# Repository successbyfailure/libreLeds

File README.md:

# libreLeds
#### Free Software and Hardware designs for controling led ligths.
libreLeds is a combination of firmware, control app and pcbs that allows you to build led_enabled gadgets. 
#### All libre for you!.

### Getting started:

 -Flash firmware on the esp8266 via arduino ide.

 -Flash extra data via:
 https://github.com/esp8266/arduino-esp8266fs-plugin

 -Install app on your phone, set it to host a wifi AP named "ledMaster" with pass "clubmate", also make sure it will be 192.168.43.1 (default on android).

 -Fire the app and turn on the esp8266, it should autoconnect to the app.
 
 -Configure Wifi and led Settings
 
 -Enjoy!

### Hardware compatible:

 -WS2812 (aka Neopixel) Strip & matrix(single & chained) through NeoPixel & NeoMatrix Library.

 -APA102 (aka DotStar)  Strip & matrix(single & chained) through FastLed Library
 
 -WS2801

### LedGadget
....

### Features:

 -Control through QT app(linux/android/mac/win).

 -Artnet support (DMX over wifi).

 -Music analizer with MSGEQ7 (vuLevel, spectrum, peak, bpms)

 -Color Effects.

 -Effect Playlist.

 -Http Updater.

 -Http file uploader.

### Known things:
 -Stop the animations before changing the led config, shit can happen otherwise.
 -In AP mode there is a memory leak and in some minutes you loose remote control.

### Setup environment:
-Compile firmware:
You will need latest arduino with esp8266 support from:
https://github.com/esp8266/Arduino
Fastled Library from:
https://github.com/FastLED/FastLED/releases
Neopixel, matrix and gfx from adafruit.
https://learn.adafruit.com/adafruit-arduino-ide-setup/arduino-1-dot-6-x-ide

the libraries included in the dependencies folder.

-Compile app
latest QT for the desktop app, also android sdk for compiling android app.

### Wifi Modes:
...Explain here...

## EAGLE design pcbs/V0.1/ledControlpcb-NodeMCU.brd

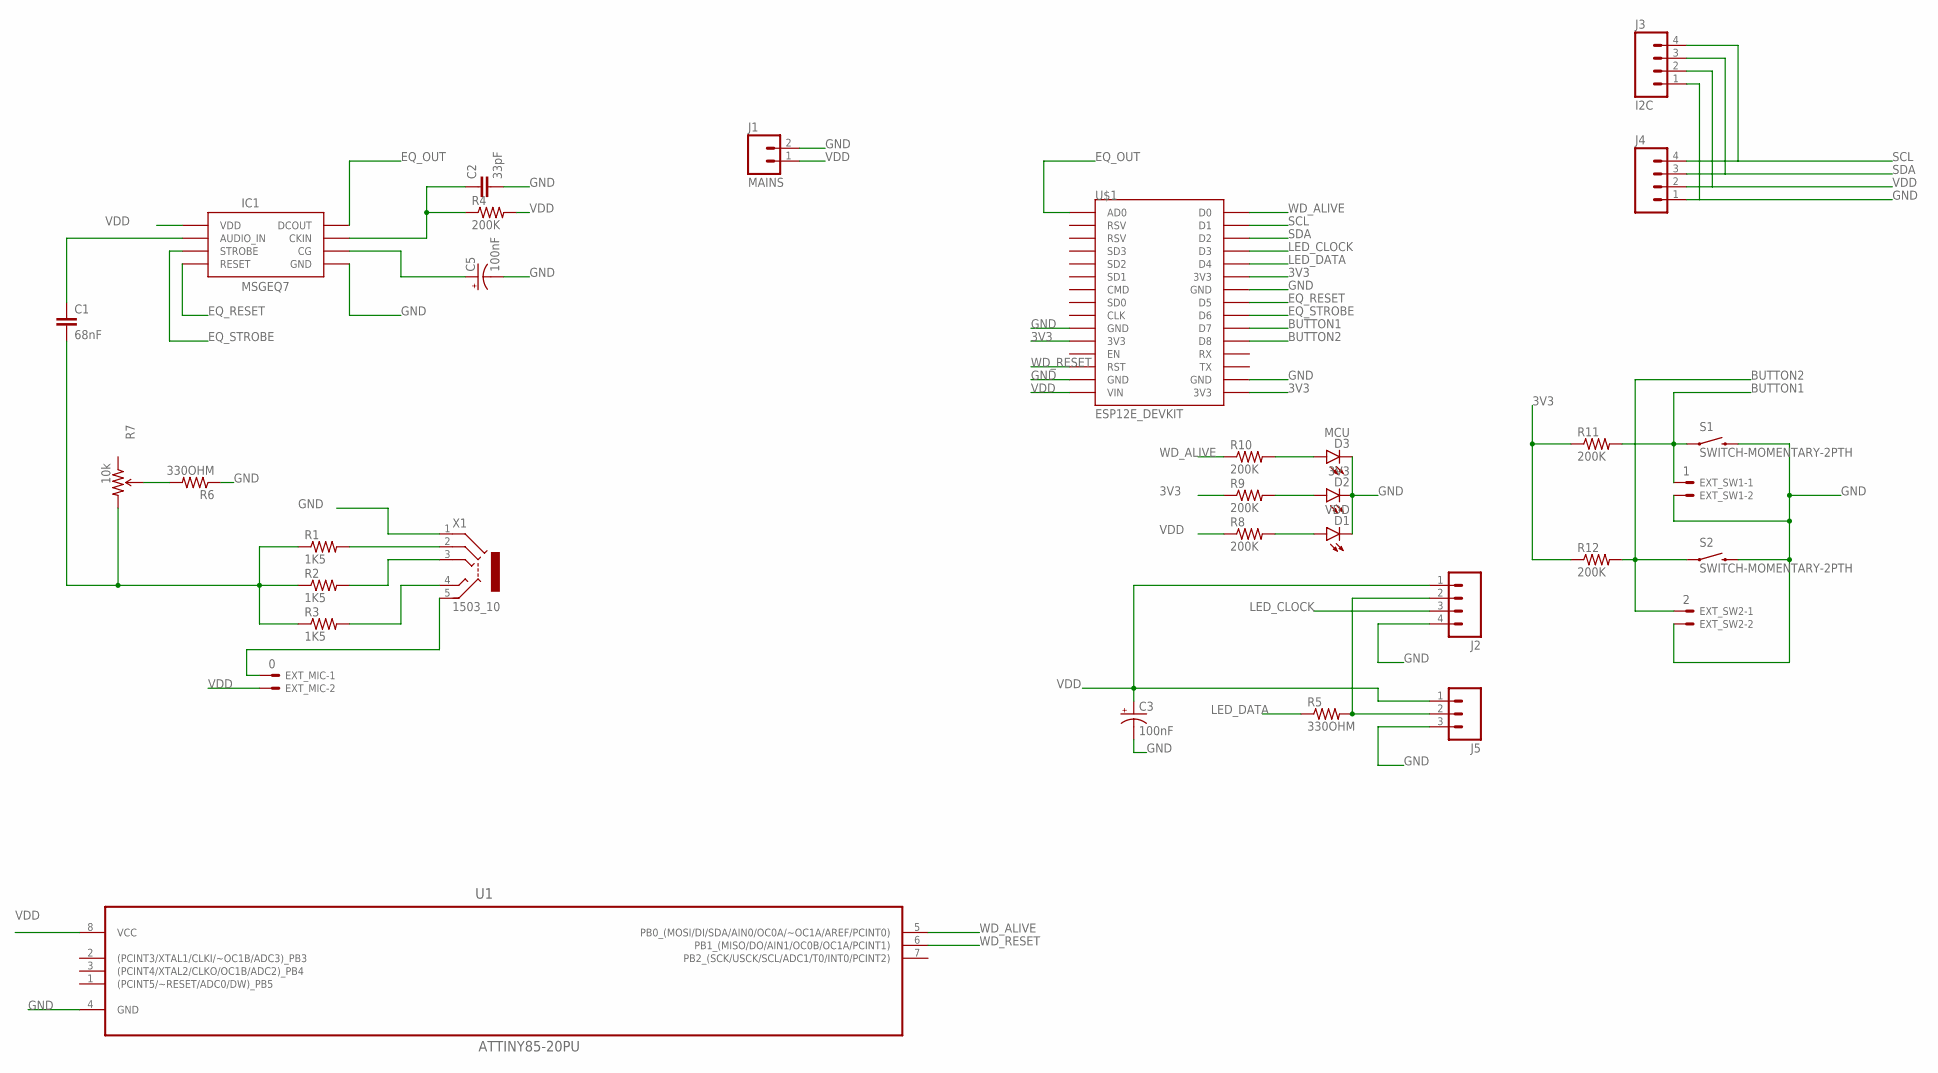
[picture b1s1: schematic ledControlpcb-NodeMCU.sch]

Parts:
C1: 68nF; 0603-CAP
C2: 33pF; 0603-CAP
C3, C5: 100nF; EIA3216
D1: VDD; LED-0603
D2: 3V3; LED-0603
D3: MCU; LED-0603
EXT_MIC: 0; 22-23-2021
EXT_SW1: 1; 22-23-2021
EXT_SW2: 2; 22-23-2021
IC1: MSGEQ7DIP; DIL08
J1: MAINS; JST-2-PTH-VERT
J2, J4: M04POLAR; MOLEX-1X4
J3: I2C; MOLEX-1X4
J5: M03POLAR; MOLEX-1X3
R1, R2, R3: 1K5; 0603-RES
R4, R8, R9, R10, R11, R12: 200K; 0603-RES
R5, R6: 330OHM; 0603-RES
R7: 10k; TRIM_POT_PTH
S1, S2: SWITCH-MOMENTARY-2PTH; TACTILE-PTH
U1: ATTINY85-20PU; DIP254P762X533-8
U$1: ESP12E_DEVKIT
X1: 1503_10

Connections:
3V3: R9.1, R11.1, R12.1, U$1.3V3@0 (3V3), U$1.3V3@1 (3V3), U$1.3V3@2 (3V3)
AUDIO_IN: C1.2, R1.1, R2.1, R3.1, R7.3 (CW)
BUTTON1: EXT_SW1.1, R11.2, S1.1, U$1.D7
BUTTON2: EXT_SW2.1, R12.2, S2.1, U$1.D8
EQ_OUT: IC1.3 (DCOUT), U$1.AD0
EQ_RESET: IC1.7 (RESET), U$1.D5
EQ_STROBE: IC1.4 (STROBE), U$1.D6
GND: C2.2, C3.C (-), C5.C (-), D1.C, D2.C, D3.C, EXT_SW1.2, EXT_SW2.2, IC1.2 (GND), J1.2, J2.4, J3.1, J4.1, J5.3, R6.1, S1.3 (2), S2.3 (2), U1.4 (GND), U$1.GND@0 (GND), U$1.GND@1 (GND), U$1.GND@2 (GND), U$1.GND@3 (GND), X1.1
LED_CLOCK: J2.3, U$1.D3
LED_DATA: R5.1, U$1.D4
unnamed: R1.2, X1.2
unnamed: R2.2, X1.3
unnamed: R3.2, X1.4
unnamed: C1.1, IC1.5 (AUDIO_IN)
unnamed: R6.2, R7.2 (WIPER)
unnamed: D3.A, R10.2
unnamed: C5.A (+), IC1.6 (CG)
unnamed: C2.1, IC1.8 (CKIN), R4.1
unnamed: D2.A, R9.2
unnamed: J2.2, J5.2, R5.2
unnamed: D1.A, R8.2
unnamed: EXT_MIC.1, X1.5
SCL: J3.4, J4.4, U$1.D1
SDA: J3.3, J4.3, U$1.D2
VDD: C3.A (+), EXT_MIC.2, IC1.1 (VDD), J1.1, J2.1, J3.2, J4.2, J5.1, R4.2, R8.1, U1.8 (VCC), U$1.VIN
WD_ALIVE: R10.1, U1.5 (PB0_(MOSI/DI/SDA/AIN0/OC0A/~OC1A/AREF/P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), U$1.D0
WD_RESET: U1.6 (PB1_(MISO/DO/AIN1/OC0B/OC1A/PCINT1)), U$1.RST

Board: 2 copper layers, 33 parts (12 on the bottom side), 27 nets, no tracks yet.

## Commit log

2016-10-31 ignore qt build paths and .pro .user files new file: .gitignore
2016-10-31 libreLeds V0.1
    Primera carga del repo.
    -Firmware libreLeds
    -Aplicacion QT de control
2016-10-31 archivos eagle de las pcbs + modelo3d pcb
2016-11-01 modelo 3d para el panel de leds
2016-11-02 añadida libreria de neopixel modificada
2016-11-02 animacion de inicio
2016-11-02 ahora si incluida la libreria modificada
2016-11-03 Animacion de inicio
    Efectos
    Cambios en la ui
    Soporte Spifs y cargador web de archivos sacado del ejemplo del esp
2016-11-07 carcasa para el panel de leds
2016-11-07 cambios en la ui
2016-11-10 Mejoras en la ui entre otras
2016-11-10 modo server para la app movil
    apk para android
2016-11-14 -Algunos bugs de la interfaz arreglados, quedan mas. -Cambios en la interfaz para hacerla mas manejable en android -Nuevo selector de color -La barra de brillo no funciona.
2016-11-15 mas bug hunting.
    mejoras en la carcasa
2016-11-18 habilitado ledWheel
2016-11-19 mejoras aqui y alla
2016-11-19 ajustes en la interfaz
2016-11-30 añadido soporte para los WS2801
2017-01-06 arbol de navidad y caja para la electronica del panel
2017-03-07 fixes dmx
2017-03-07 carcasa fuente panel
2017-03-07 eliminado autosalvado antiguo
2017-03-20 fixes para el merkaba
2017-06-08 contador de tramas dmx incorrectas
2017-06-08 repo sync
2017-06-28 contador de paquetes dmx y salida serie
2017-06-28 añadido gadget libreSaber
2017-06-28 soporte experimental para los botones
2017-07-03 esqueleto de metodos para las animaciones del laser
2017-07-03 añadido Color por defecto a los settings
2017-07-06 añadido soporte para adafruit rgbw
2017-07-07 debug de la tira rgbw
2017-07-07 bug hunting 1
2018-08-03 fixes para la ultima version del framework, de momento problemas con la ip statica
2018-08-04 arreglado el bug de la ip fija. soporte para el cacharro kinetico
2018-08-05 minor fixes
    minor fixes
2018-08-05 Sistema de adaptacion del brillo en caso de descenso del voltaje
2018-09-03 Nuevo nodo y arquitectura
2018-09-03 calibracion de potencia en el arranque
2018-09-03 ajustes
2018-09-04 Mergue de funcionalidad ledGadget, bug por encontrar....
2018-09-05 ajustes a los efectos
2018-09-06 no se muy bien que pero cosas varias

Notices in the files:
parts and their libraries:
SparkFun-Resistors: Licensing: Creative Commons ShareAlike 4.0 International - https://creativecommons.org/licenses/by-sa/4.0
